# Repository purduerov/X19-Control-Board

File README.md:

# X19 Control Board

Primary microcontroller board managing actuator actuation, telemetry collection, and vehicle subsystem communication for the Purdue ROV X19 vehicle.

---

## 🚀 Quickstart: Opening the Project (Recommended)

**Always open the project using the 1-click launcher:**

* **Windows:** Double-click `LAUNCH_KICAD.bat`
* **macOS / Linux:** Run `./LAUNCH_KICAD.sh`

### What the Launcher Does Automatically:
1. ⚙️ **Configures Git Hooks & Clean Filters:** Sets up Git to strip volatile viewport/zoom coordinates on every commit, preventing merge conflicts.
2. 🔄 **Auto-Updates Component Library:** Pulls the freshest symbols, footprints, and 3D models from `purdue-rov-kicad-lib` before opening.
3. 📐 **Opens KiCad:** Launches `X19-Control-Board.kicad_pro` with all 6 central library categories pre-linked.

---

## Cloning the Repository
Clone recursively to ensure the central component library is initialized:
```bash
git clone --recursive https://github.com/purduerov/X19-Control-Board.git
cd X19-Control-Board
```

## Central Component Library & Manager GUI

The project links to the central `purdue-rov-kicad-lib` submodule mapped across 6 categories in `sym-lib-table` and `fp-lib-table`:
- `rov_passives`: Resistors, capacitors, inductors, crystals
- `rov_power`: Voltage regulators, buck/boost converters, MOSFETs, diodes
- `rov_logic`: MCUs, logic ICs, op-amps, drivers, level shifters
- `rov_connectors`: Power terminals, XT60, headers, USB, JST connectors
- `rov_sensors`: IMUs, temperature, pressure sensors
- `rov_mech`: Mounting holes, standoffs, test points

### Launching the Library Manager GUI
To browse parts, inspect footprints, edit properties, or add/delete components in the shared library:
- **Windows:** Double-click `libs\purdue-rov-kicad-lib\LIBRARY_MANAGER.bat`
- **macOS / Linux:** Run `./libs/purdue-rov-kicad-lib/LIBRARY_MANAGER.sh`

## Design Rules & Clearances

- Clearance and isolation constraints are configured in `custom_rules.kicad_dru`.
- All symbols and footprints must comply with central library guidelines.

## Automated CI/CD & DevOps Preflight Checks

All CI/CD automation and tooling are centralized in [`purduerov/pcb-devops`](https://github.com/purduerov/pcb-devops):
1. **Automated Git Clean Filters:** Configured automatically by `.githooks/pre-commit` to prevent viewport/zoom merge noise.
2. **KiCad Symbol Linting:** Validates mandatory fields (`MPN`, `Manufacturer`, `Category`, `DigiKey`, `Datasheet`, `Temp_Range`) on all library components.
3. **ERC & DRC Validation:** Executes Electrical and Design Rules Checks via KiBot in GitHub Actions.
4. **Artifact Generation:** Automatically exports Schematic PDFs, Board Layout PDFs, and Interactive HTML BOMs on every pull request.

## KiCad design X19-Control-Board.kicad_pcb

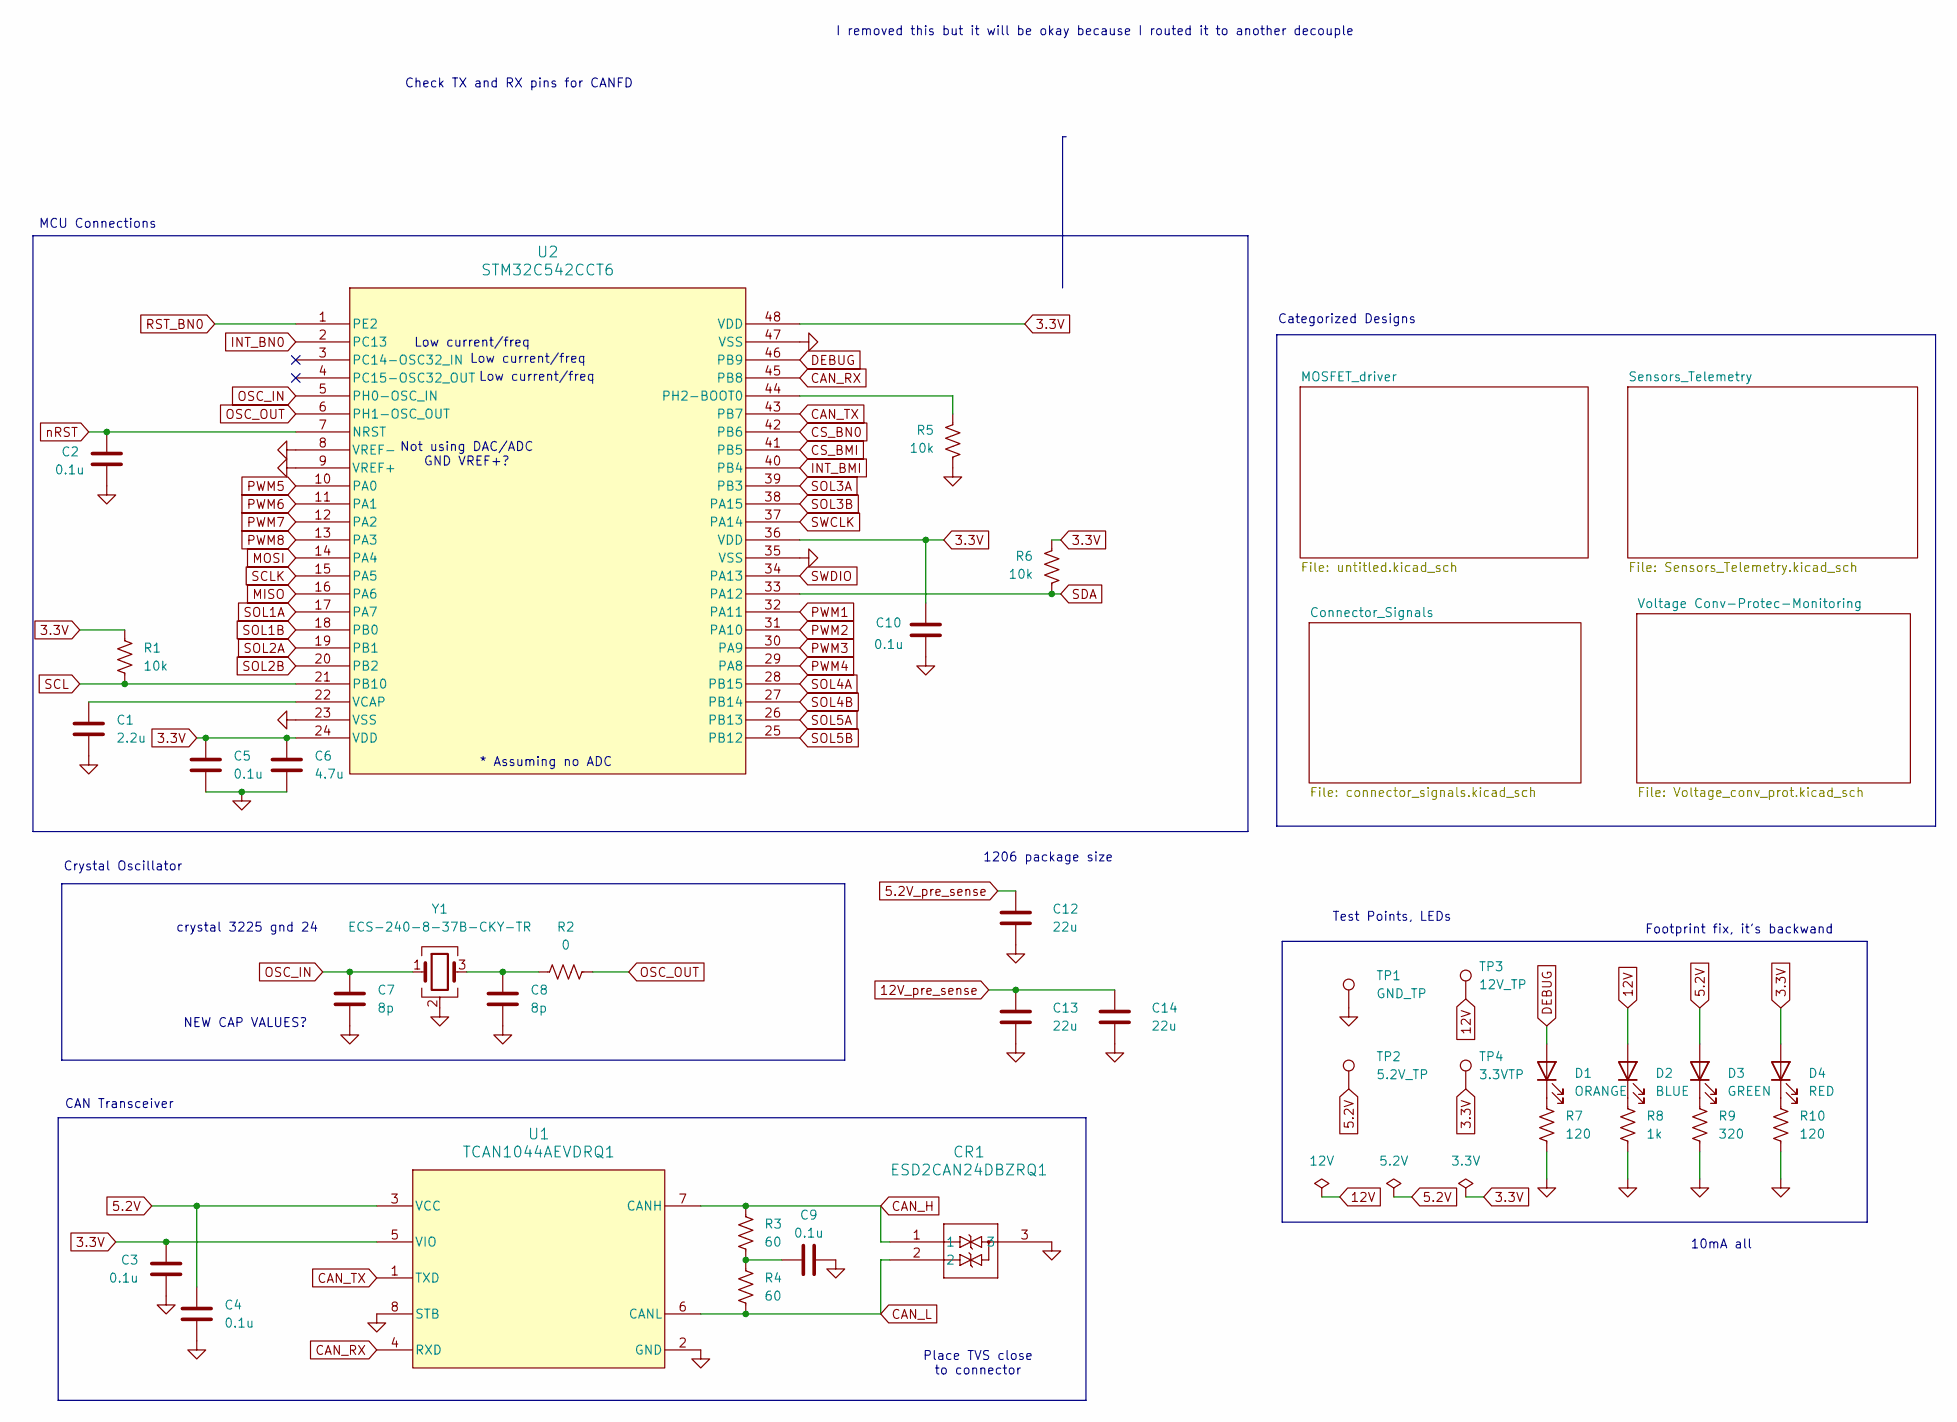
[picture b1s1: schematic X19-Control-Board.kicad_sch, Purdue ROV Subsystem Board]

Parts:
C1: 2.2u; C_0603_1608Metric_Pad1.08x0.95mm_HandSolder
C2, C3, C4, C5, C9, C10: 0.1u; C_0603_1608Metric_Pad1.08x0.95mm_HandSolder
C6: 4.7u; C_0603_1608Metric_Pad1.08x0.95mm_HandSolder
C7, C8: 8p; C_0603_1608Metric_Pad1.08x0.95mm_HandSolder
C12, C13, C14: 22u; C_1206_3216Metric_Pad1.33x1.80mm_HandSolder
CR1: ESD2CAN24DBZRQ1
D1: ORANGE; LTST-C191KFKT_1_anode_2_cathode
D2: BLUE; LTST-C191KFKT_1_anode_2_cathode
D3: GREEN; LTST-C191KFKT_1_anode_2_cathode
D4: RED; LTST-C191KFKT_1_anode_2_cathode
R1, R5, R6: 10k; R_0603_1608Metric_Pad0.98x0.95mm_HandSolder
R2: 0; R_0603_1608Metric_Pad0.98x0.95mm_HandSolder
R3, R4: 60; R_0603_1608Metric_Pad0.98x0.95mm_HandSolder
R7, R10: 120; R_0603_1608Metric_Pad0.98x0.95mm_HandSolder
R8: 1k; R_0603_1608Metric_Pad0.98x0.95mm_HandSolder
R9: 320; R_0603_1608Metric_Pad0.98x0.95mm_HandSolder
TP1: GND_TP; TestPoint_Pad_D3.0mm
TP2: 5.2V_TP; TestPoint_Pad_D3.0mm
TP3: 12V_TP; TestPoint_Pad_D3.0mm
TP4: 3.3VTP; TestPoint_Pad_D3.0mm
U1: TCAN1044AEVDRQ1
U2: STM32C542CCT6
Y1: ECS-240-8-37B-CKY-TR; ECS-240-8-37CKM_ECS

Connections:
3.3V: C3.1, C5.1, C6.1, C10.2, D4.2 (A), R1.1, R6.1, TP4.1 (1_1), U1.5 (VIO), U2.24 (VDD), U2.36 (VDD), U2.48 (VDD); also elsewhere on the board
5.2V: C4.1, D3.2 (A), TP2.1 (1_1), U1.3 (VCC); also elsewhere on the board
5.2V_pre_sense: C12.1; also elsewhere on the board
12V: D2.2 (A), TP3.1 (1_1); also elsewhere on the board
12V_pre_sense: C13.1, C14.1; also elsewhere on the board
CAN_H: CR1.1, R3.1, U1.7 (CANH); also elsewhere on the board
CAN_L: CR1.2, R4.2, U1.6 (CANL); also elsewhere on the board
CAN_RX: U1.4 (RXD), U2.45 (PB8)
CAN_TX: U1.1 (TXD), U2.43 (PB7)
CS_BMI: U2.41 (PB5); also elsewhere on the board
CS_BN0: U2.42 (PB6); also elsewhere on the board
DEBUG: D1.2 (A), U2.46 (PB9)
GND: C1.2, C2.1, C3.2, C4.2, C5.2, C6.2, C7.2, C8.2, C9.2, C10.1, C12.2, C13.2, C14.2, CR1.3, R5.2, R7.2, R8.2, R9.2, R10.2, TP1.1 (1_1), U1.2 (GND), U1.8 (STB), U2.8 (VREF-), U2.9 (VREF+), U2.23 (VSS), U2.35 (VSS), U2.47 (VSS), Y1.2 (G), Y1.4 (G); also elsewhere on the board
INT_BMI: U2.40 (PB4); also elsewhere on the board
INT_BN0: U2.2 (PC13); also elsewhere on the board
MISO: U2.16 (PA6); also elsewhere on the board
MOSI: U2.14 (PA4); also elsewhere on the board
unnamed: C8.1, R2.1, Y1.3
unnamed: C9.1, R3.2, R4.1
unnamed: D1.1 (K), R7.1
unnamed: D2.1 (K), R8.1
unnamed: D3.1 (K), R9.1
unnamed: D4.1 (K), R10.1
unnamed: R5.1, U2.44 (PH2-BOOT0)
unnamed: C1.1, U2.22 (VCAP)
OSC_IN: C7.1, U2.5 (PH0-OSC_IN), Y1.1
OSC_OUT: R2.2, U2.6 (PH1-OSC_OUT)
PWM1: U2.32 (PA11); also elsewhere on the board
PWM2: U2.31 (PA10); also elsewhere on the board
PWM3: U2.30 (PA9); also elsewhere on the board
PWM4: U2.29 (PA8); also elsewhere on the board
PWM5: U2.10 (PA0); also elsewhere on the board
PWM6: U2.11 (PA1); also elsewhere on the board
PWM7: U2.12 (PA2); also elsewhere on the board
PWM8: U2.13 (PA3); also elsewhere on the board
RST_BN0: U2.1 (PE2); also elsewhere on the board
SCL: R1.2, U2.21 (PB10); also elsewhere on the board
SCLK: U2.15 (PA5); also elsewhere on the board
SDA: R6.2, U2.33 (PA12); also elsewhere on the board
SOL1A: U2.17 (PA7); also elsewhere on the board
SOL1B: U2.18 (PB0); also elsewhere on the board
SOL2A: U2.19 (PB1); also elsewhere on the board
SOL2B: U2.20 (PB2); also elsewhere on the board
SOL3A: U2.39 (PB3); also elsewhere on the board
SOL3B: U2.38 (PA15); also elsewhere on the board
SOL4A: U2.28 (PB15); also elsewhere on the board
SOL4B: U2.27 (PB14); also elsewhere on the board
SOL5A: U2.26 (PB13); also elsewhere on the board
SOL5B: U2.25 (PB12); also elsewhere on the board
SWCLK: U2.37 (PA14); also elsewhere on the board
SWDIO: U2.34 (PA13); also elsewhere on the board
nRST: C2.2, U2.7 (NRST); also elsewhere on the board

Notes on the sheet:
Test Points, LEDs
Low current/freq
I removed this but it will be okay because I routed it to another decouple
CAN Transceiver
* Assuming no ADC
1206 package size
Crystal Oscillator
Not using DAC/ADC GND VREF+?
NEW CAP VALUES?
Check TX and RX pins for CANFD
MCU Connections
10mA all
crystal 3225 gnd 24
Footprint fix, it's backwand
Place TVS close to connector
Categorized Designs

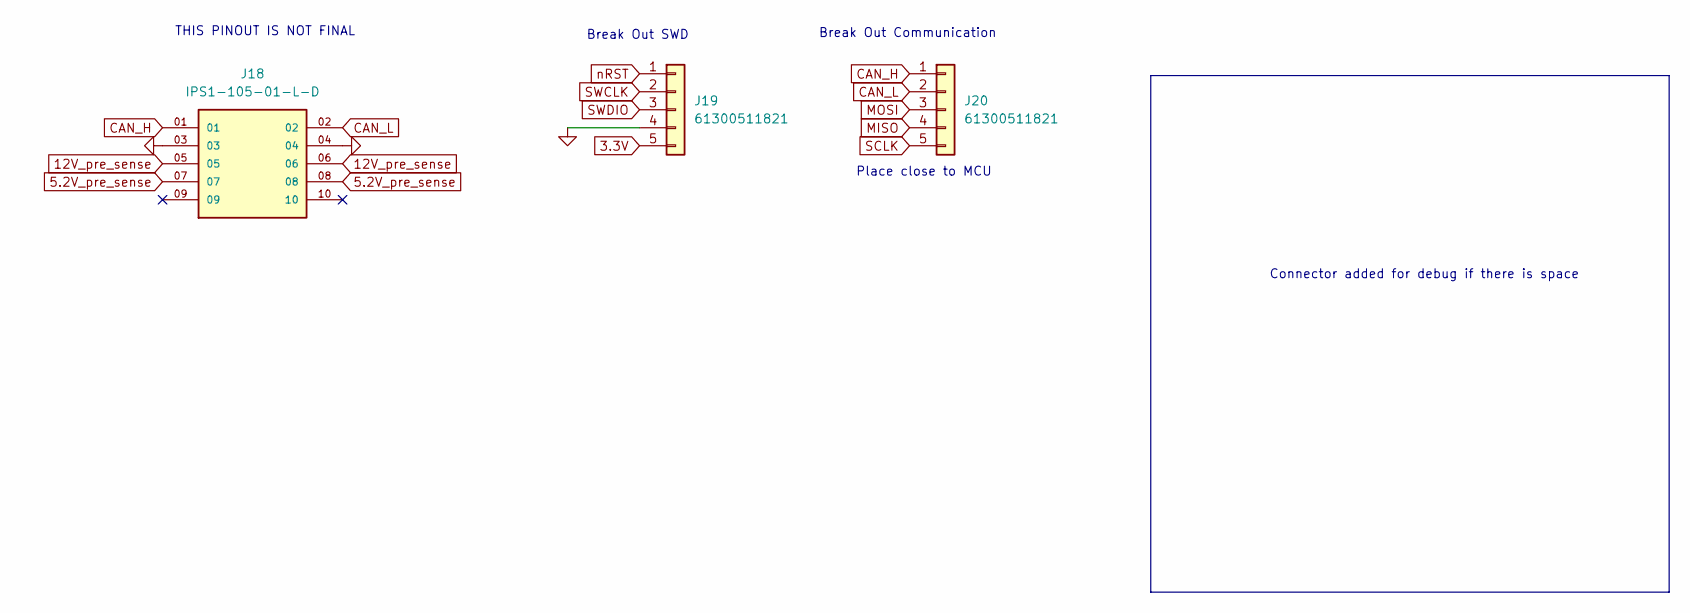
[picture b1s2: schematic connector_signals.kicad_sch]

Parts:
J18: IPS1-105-01-L-D; SAMTEC_IPS1-105-01-S-D; PARTREV R
J19, J20: 61300511821

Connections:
3.3V: J19.5; also elsewhere on the board
5.2V_pre_sense: J18.07, J18.08; also elsewhere on the board
12V_pre_sense: J18.05, J18.06; also elsewhere on the board
CAN_H: J18.01, J20.1; also elsewhere on the board
CAN_L: J18.02, J20.2; also elsewhere on the board
GND: J18.03, J18.04, J19.4; also elsewhere on the board
MISO: J20.4; also elsewhere on the board
MOSI: J20.3; also elsewhere on the board
SCLK: J20.5; also elsewhere on the board
SWCLK: J19.2; also elsewhere on the board
SWDIO: J19.3; also elsewhere on the board
nRST: J19.1; also elsewhere on the board

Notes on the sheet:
Break Out Communication
Place close to MCU
Connector added for debug if there is space
THIS PINOUT IS NOT FINAL
Break Out SWD

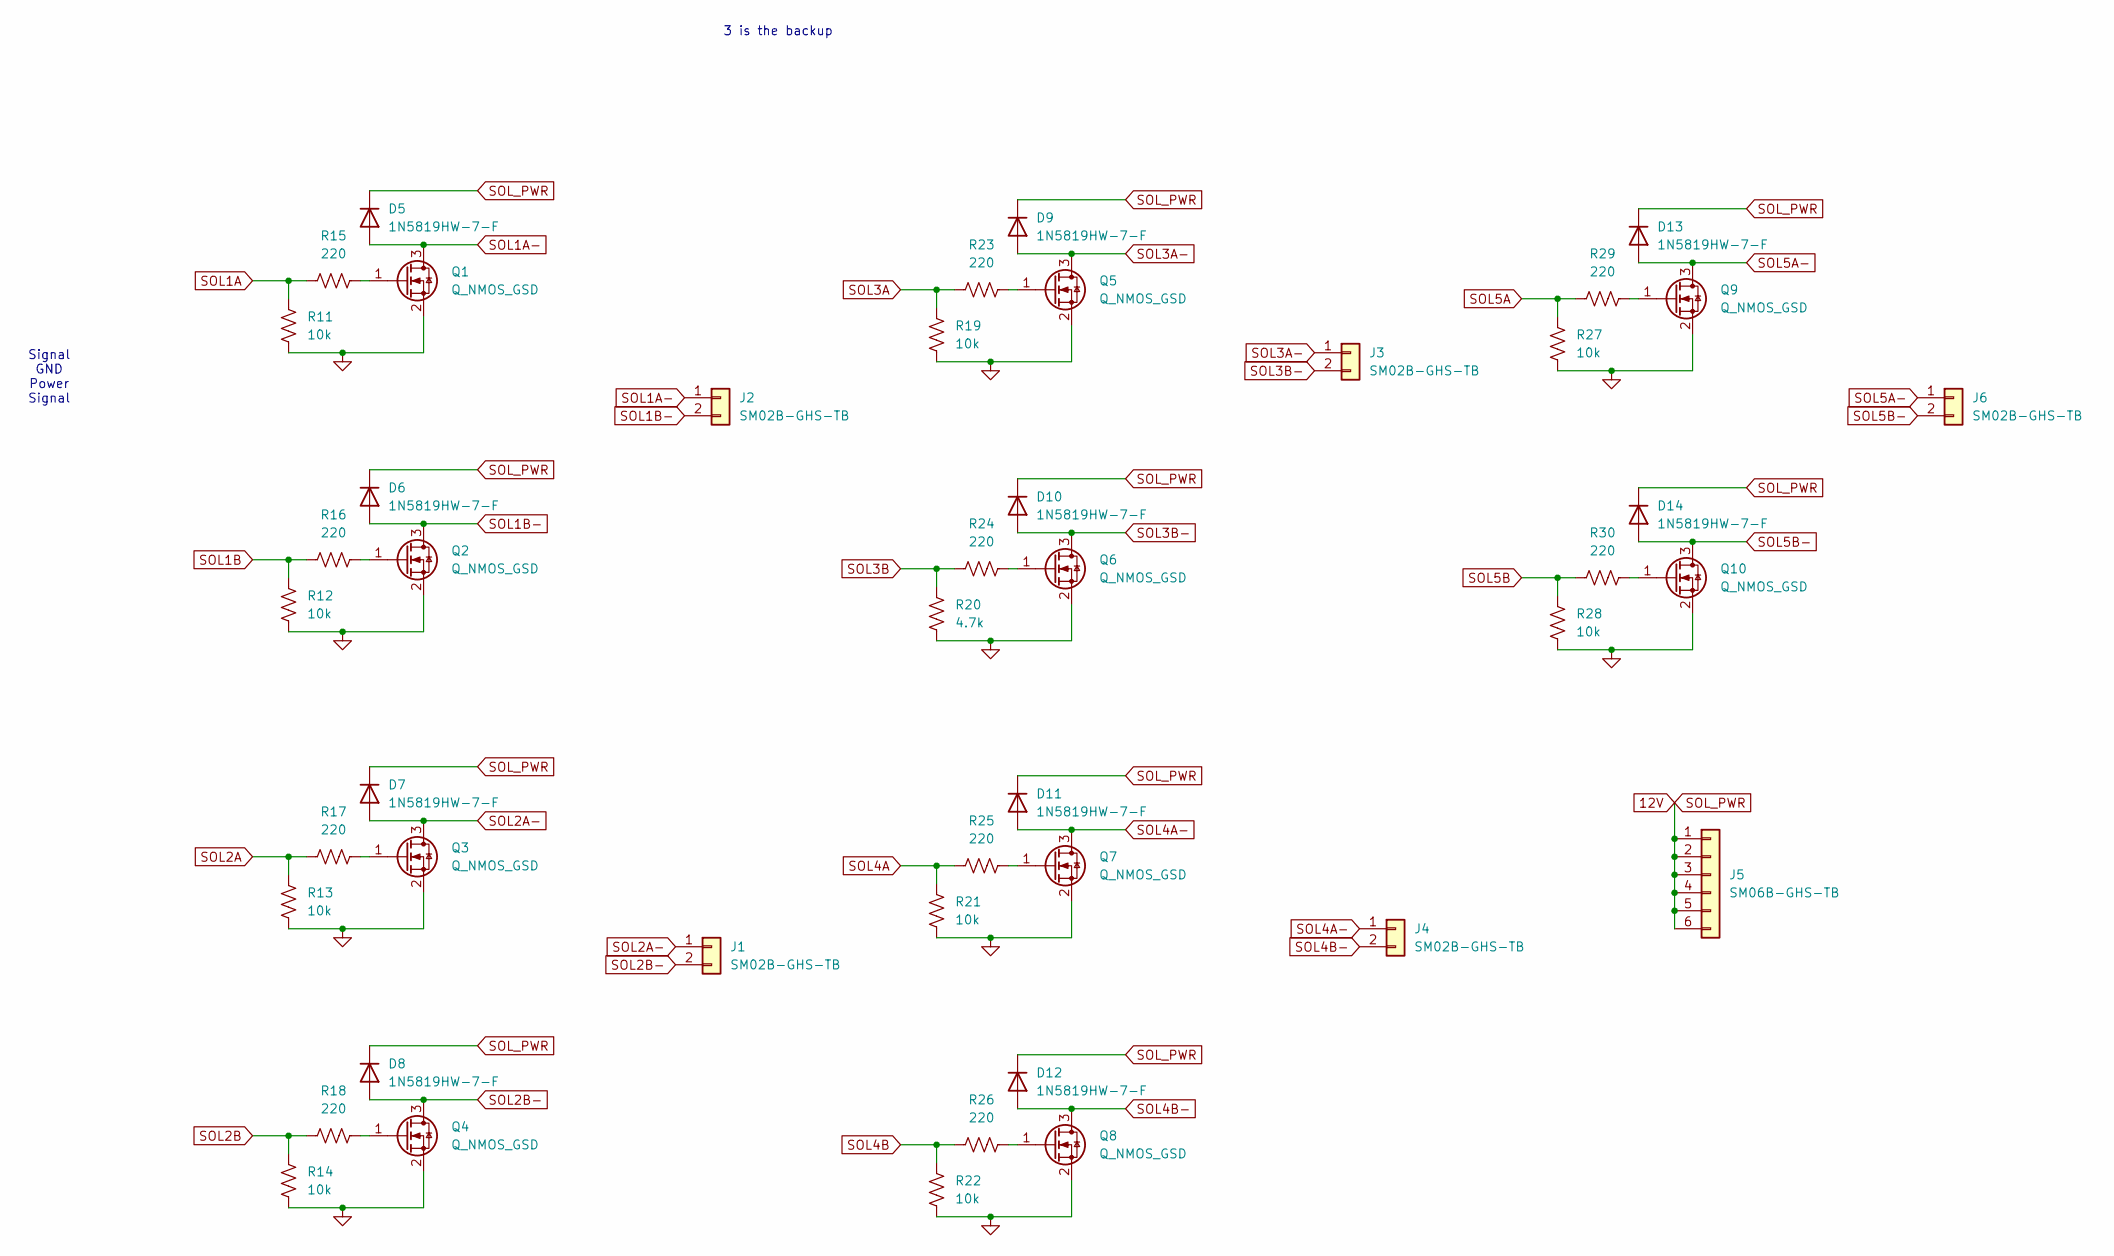
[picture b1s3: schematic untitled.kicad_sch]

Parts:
D5, D6, D7, D8, D9, D10, D11, D12, D13, D14: 1N5819HW-7-F; 1N5819HW-7-F_DIO
J1, J2, J3, J4, J6: SM02B-GHS-TB; Vertical_CONN_BM02B-GHS-TBT_JST
J5: SM06B-GHS-TB; vertical_CONN_BM06B-GHS-TBT_JST
Q1, Q2, Q3, Q4, Q5, Q6, Q7, Q8, Q9, Q10: Q_NMOS_GSD; SOT-23-3L_AOS
R11, R12, R13, R14, R19, R21, R22, R27, R28: 10k; R_0603_1608Metric_Pad0.98x0.95mm_HandSolder
R15, R16, R17, R18, R23, R24, R25, R26, R29, R30: 220; R_0603_1608Metric_Pad0.98x0.95mm_HandSolder
R20: 4.7k; R_0603_1608Metric_Pad0.98x0.95mm_HandSolder

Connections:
12V: D5.1 (K), D6.1 (K), D7.1 (K), D8.1 (K), D9.1 (K), D10.1 (K), D11.1 (K), D12.1 (K), D13.1 (K), D14.1 (K), J5.1, J5.2, J5.3, J5.4, J5.5, J5.6; also elsewhere on the board
GND: Q1.2 (S), Q2.2 (S), Q3.2 (S), Q4.2 (S), Q5.2 (S), Q6.2 (S), Q7.2 (S), Q8.2 (S), Q9.2 (S), Q10.2 (S), R11.2, R12.2, R13.2, R14.2, R19.2, R20.2, R21.2, R22.2, R27.2, R28.2; also elsewhere on the board
unnamed: Q1.1 (G), R15.2
unnamed: Q2.1 (G), R16.2
unnamed: Q3.1 (G), R17.2
unnamed: Q4.1 (G), R18.2
unnamed: Q5.1 (G), R23.2
unnamed: Q6.1 (G), R24.2
unnamed: Q7.1 (G), R25.2
unnamed: Q8.1 (G), R26.2
unnamed: Q9.1 (G), R29.2
unnamed: Q10.1 (G), R30.2
SOL1A: R11.1, R15.1; also elsewhere on the board
SOL1A-: D5.2 (A), J2.1, Q1.3 (D)
SOL1B: R12.1, R16.1; also elsewhere on the board
SOL1B-: D6.2 (A), J2.2, Q2.3 (D)
SOL2A: R13.1, R17.1; also elsewhere on the board
SOL2A-: D7.2 (A), J1.1, Q3.3 (D)
SOL2B: R14.1, R18.1; also elsewhere on the board
SOL2B-: D8.2 (A), J1.2, Q4.3 (D)
SOL3A: R19.1, R23.1; also elsewhere on the board
SOL3A-: D9.2 (A), J3.1, Q5.3 (D)
SOL3B: R20.1, R24.1; also elsewhere on the board
SOL3B-: D10.2 (A), J3.2, Q6.3 (D)
SOL4A: R21.1, R25.1; also elsewhere on the board
SOL4A-: D11.2 (A), J4.1, Q7.3 (D)
SOL4B: R22.1, R26.1; also elsewhere on the board
SOL4B-: D12.2 (A), J4.2, Q8.3 (D)
SOL5A: R27.1, R29.1; also elsewhere on the board
SOL5A-: D13.2 (A), J6.1, Q9.3 (D)
SOL5B: R28.1, R30.1; also elsewhere on the board
SOL5B-: D14.2 (A), J6.2, Q10.3 (D)

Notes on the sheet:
3 is the backup
Signal GND Power Signal

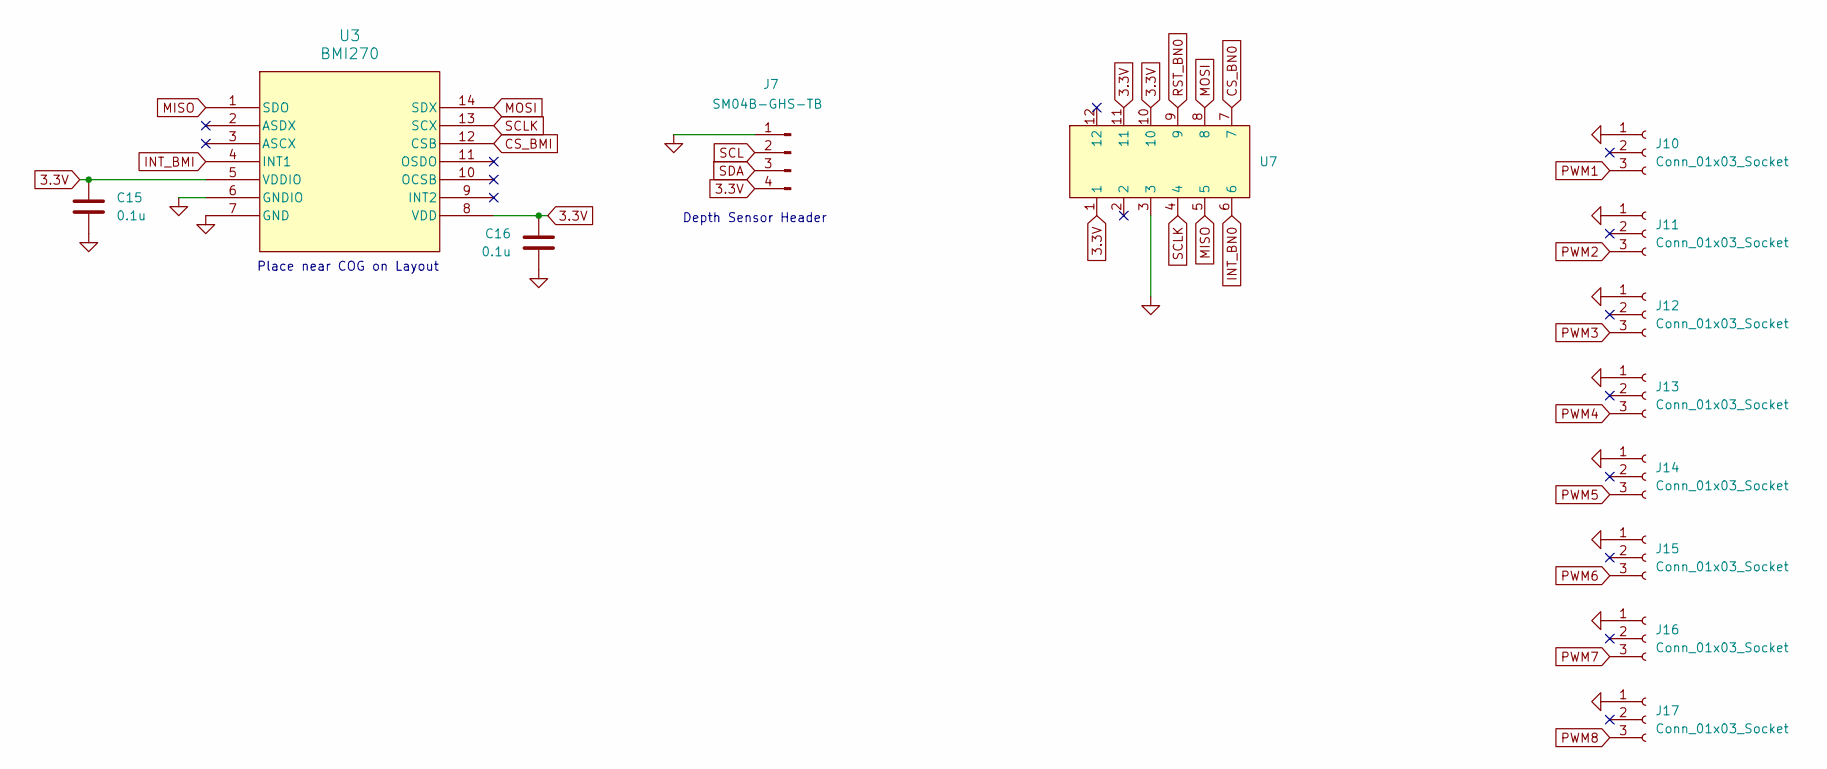
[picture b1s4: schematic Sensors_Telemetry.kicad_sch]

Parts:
C15, C16: 0.1u; C_0603_1608Metric_Pad1.08x0.95mm_HandSolder
J7: SM04B-GHS-TB; vertical_CONN_BM04B-GHS-TBT_JST
J10, J11, J12, J13, J14, J15, J16, J17: Conn_01x03_Socket; PinHeader_1x03_P2.54mm_Vertical
U3: BMI270; BMI270_BOS
U7: MODULE_4754

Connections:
3.3V: C15.1, C16.1, J7.4, U3.5 (VDDIO), U3.8 (VDD), U7.1, U7.10, U7.11; also elsewhere on the board
CS_BMI: U3.12 (CSB); also elsewhere on the board
CS_BN0: U7.7; also elsewhere on the board
GND: C15.2, C16.2, J7.1, J10.1, J11.1, J12.1, J13.1, J14.1, J15.1, J16.1, J17.1, U3.6 (GNDIO), U3.7 (GND), U7.3; also elsewhere on the board
INT_BMI: U3.4 (INT1); also elsewhere on the board
INT_BN0: U7.6; also elsewhere on the board
MISO: U3.1 (SDO), U7.5; also elsewhere on the board
MOSI: U3.14 (SDX), U7.8; also elsewhere on the board
PWM1: J10.3; also elsewhere on the board
PWM2: J11.3; also elsewhere on the board
PWM3: J12.3; also elsewhere on the board
PWM4: J13.3; also elsewhere on the board
PWM5: J14.3; also elsewhere on the board
PWM6: J15.3; also elsewhere on the board
PWM7: J16.3; also elsewhere on the board
PWM8: J17.3; also elsewhere on the board
RST_BN0: U7.9; also elsewhere on the board
SCL: J7.2; also elsewhere on the board
SCLK: U3.13 (SCX), U7.4; also elsewhere on the board
SDA: J7.3; also elsewhere on the board

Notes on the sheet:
Place near COG on Layout
Depth Sensor Header

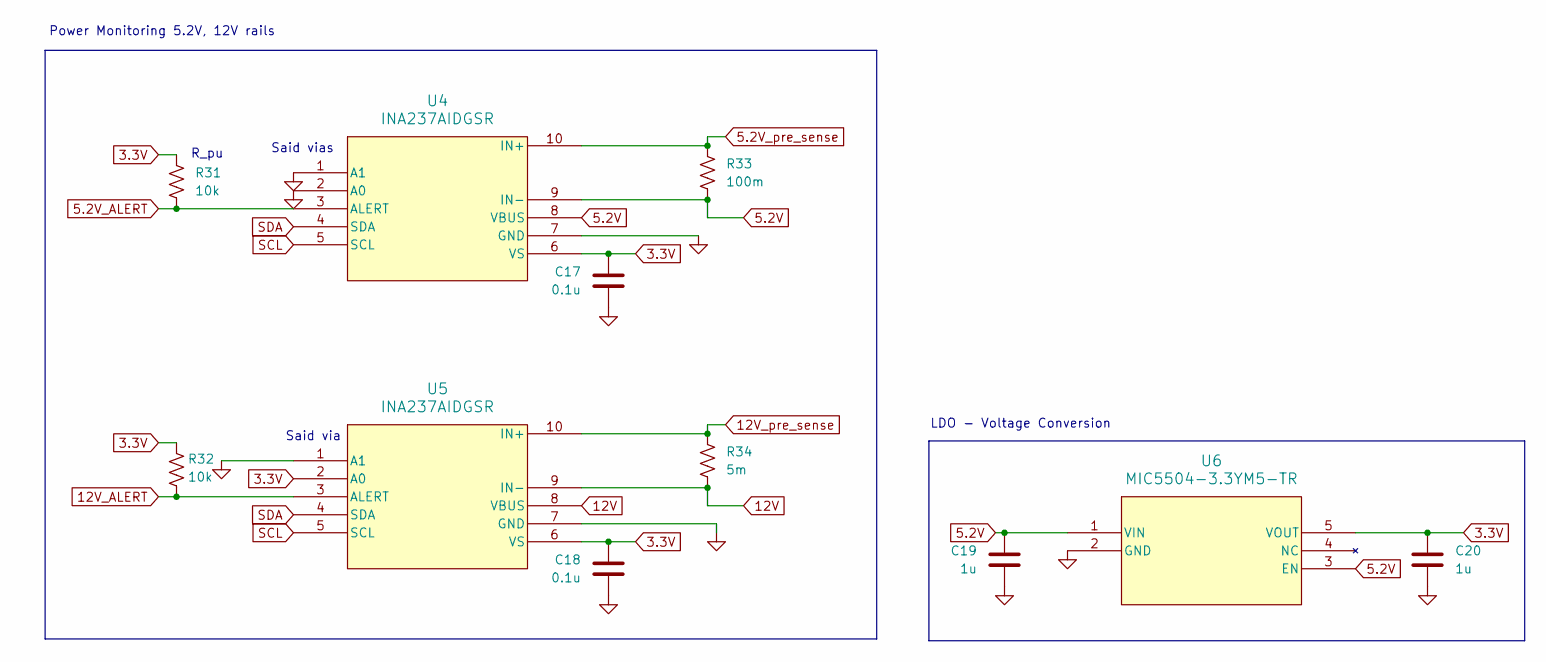
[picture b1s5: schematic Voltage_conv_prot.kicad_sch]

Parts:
C17, C18: 0.1u; C_0603_1608Metric_Pad1.08x0.95mm_HandSolder
C19, C20: 1u; C_0603_1608Metric_Pad1.08x0.95mm_HandSolder
R31, R32: 10k; R_0603_1608Metric_Pad0.98x0.95mm_HandSolder
R33: 100m; R_0603_1608Metric_Pad0.98x0.95mm_HandSolder
R34: 5m; R_0603_1608Metric_Pad0.98x0.95mm_HandSolder
U4, U5: INA237AIDGSR
U6: MIC5504-3.3YM5-TR; MIC5504_3_3YM5_TR

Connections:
3.3V: C17.1, C18.1, C20.1, R31.1, R32.1, U4.6 (VS), U5.2 (A0), U5.6 (VS), U6.5 (VOUT); also elsewhere on the board
5.2V: C19.1, R33.2, U4.8 (VBUS), U4.9 (IN-), U6.1 (VIN), U6.3 (EN); also elsewhere on the board
5.2V_ALERT: R31.2, U4.3 (ALERT)
5.2V_pre_sense: R33.1, U4.10 (IN+); also elsewhere on the board
12V: R34.2, U5.8 (VBUS), U5.9 (IN-); also elsewhere on the board
12V_ALERT: R32.2, U5.3 (ALERT)
12V_pre_sense: R34.1, U5.10 (IN+); also elsewhere on the board
GND: C17.2, C18.2, C19.2, C20.2, U4.1 (A1), U4.2 (A0), U4.7 (GND), U5.1 (A1), U5.7 (GND), U6.2 (GND); also elsewhere on the board
SCL: U4.5 (SCL), U5.5 (SCL); also elsewhere on the board
SDA: U4.4 (SDA), U5.4 (SDA); also elsewhere on the board

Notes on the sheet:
LDO - Voltage Conversion
Said via
R_pu
Said vias
Power Monitoring 5.2V, 12V rails

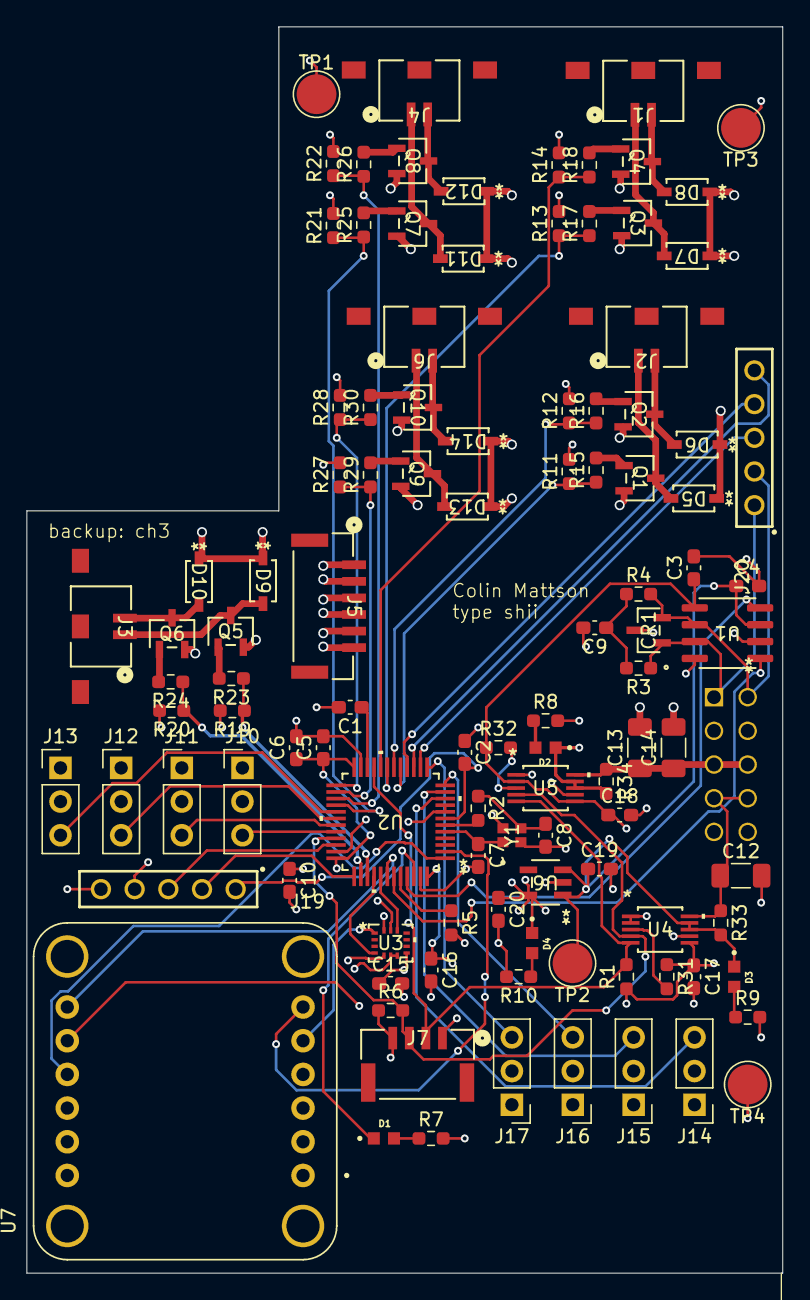
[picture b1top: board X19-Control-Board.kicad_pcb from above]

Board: 4 copper layers, 57.0 x 94.0 mm, 108 parts (1 on the bottom side), 74 nets.

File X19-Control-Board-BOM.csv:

Row,Description,Part,References,Value,Footprint,Quantity Per PCB,Status,Datasheet,KLC_S3.3,KLC_S4.1,Sim.Pins,PARTREV,STANDARD,MANUFACTURER,Sim.Device
1,Unpolarized capacitor,C,C7 C8,8p,C_0603_1608Metric_Pad1.08x0.95mm_HandSolder,2, ,,,,,,,,
2,Unpolarized capacitor,C,C2 C3 C4 C5 C9 C10 C11 C15 C16 C17 C18,0.1u,C_0603_1608Metric_Pad1.08x0.95mm_HandSolder,11, ,,,,,,,,
3,Unpolarized capacitor,C,C19 C20,1u,C_0603_1608Metric_Pad1.08x0.95mm_HandSolder,2, ,,,,,,,,
4,Unpolarized capacitor,C,C1,2.2u,C_0603_1608Metric_Pad1.08x0.95mm_HandSolder,1, ,,,,,,,,
5,Unpolarized capacitor,C,C6,4.7u,C_0603_1608Metric_Pad1.08x0.95mm_HandSolder,1, ,,,,,,,,
6,Unpolarized capacitor,C,C12 C13 C14,22u,C_1206_3216Metric_Pad1.33x1.80mm_HandSolder,3, ,,,,,,,,
7,,ESD2CAN24DBZRQ1,CR1,SOT-23_DBZ_TEX,ESD2CAN24DBZRQ1,1, ,ESD2CAN24DBZRQ1,,,,,,,
8,Diode,D,D5 D6 D7 D8 D9 D10 D11 D12 D13 D14,1N5819HW-7-F,1N5819HW-7-F_DIO,10, ,,,,1=K 2=A,,,,D
9,Light emitting diode,LED,D2,BLUE,LTST-C191KFKT_1_anode_2_cathode,1, ,,,,1=K 2=A,,,,
10,Light emitting diode,LED,D3,GREEN,LTST-C191KFKT_1_anode_2_cathode,1, ,,,,1=K 2=A,,,,
11,Light emitting diode,LED,D1,ORANGE,LTST-C191KFKT_1_anode_2_cathode,1, ,,,,1=K 2=A,,,,
12,Light emitting diode,LED,D4,RED,LTST-C191KFKT_1_anode_2_cathode,1, ,,,,1=K 2=A,,,,
13,"Generic connector, single row, 01x05, script generated (kicad-library-utils/schlib/autogen/connector/)",Conn_01x05,J19 J20,61300511821,61300511821,2, ,,,,,,,,
14,"Generic connector, single row, 01x03, script generated",Conn_01x03_Socket,J10 J11 J12 J13 J14 J15 J16 J17,Conn_01x03_Socket,PinHeader_1x03_P2.54mm_Vertical,8, ,,,,,,,,
15,,IPS1-105-01-L-D,J18,IPS1-105-01-L-D,SAMTEC_IPS1-105-01-S-D,1, ,,,,,R,Manufacturer Recommendations,Samtec,
16,"Generic connector, single row, 01x02, script generated (kicad-library-utils/schlib/autogen/connector/)",Conn_01x02,J1 J2 J3 J4 J6,SM02B-GHS-TB,Vertical_CONN_BM02B-GHS-TBT_JST,5, ,,,,,,,,
17,"Generic connector, single row, 01x04, script generated",Conn_01x04_Pin,J7,SM04B-GHS-TB,vertical_CONN_BM04B-GHS-TBT_JST,1, ,,,,,,,,
18,"Generic connector, single row, 01x06, script generated (kicad-library-utils/schlib/autogen/connector/)",Conn_01x06,J5,SM06B-GHS-TB,vertical_CONN_BM06B-GHS-TBT_JST,1, ,,,,,,,,
19,"N-MOSFET transistor, gate/source/drain",Q_NMOS_GSD,Q1 Q2 Q3 Q4 Q5 Q6 Q7 Q8 Q9 Q10,Q_NMOS_GSD,SOT-23-3L_AOS,10, ,,,,,,,,
20,"Resistor, US symbol",R_US,R2,0,R_0603_1608Metric_Pad0.98x0.95mm_HandSolder,1, ,,,,,,,,
21,"Resistor, US symbol",R_US,R34,5m,R_0603_1608Metric_Pad0.98x0.95mm_HandSolder,1, ,,,,,,,,
22,"Resistor, US symbol",R_US,R33,100m,R_0603_1608Metric_Pad0.98x0.95mm_HandSolder,1, ,,,,,,,,
23,"Resistor, US symbol",R_US,R3 R4,60,R_0603_1608Metric_Pad0.98x0.95mm_HandSolder,2, ,,,,,,,,
24,"Resistor, US symbol",R_US,R7 R10,120,R_0603_1608Metric_Pad0.98x0.95mm_HandSolder,2, ,,,,,,,,
25,"Resistor, US symbol",R_US,R15 R16 R17 R18 R23 R24 R25 R26 R29 R30,220,R_0603_1608Metric_Pad0.98x0.95mm_HandSolder,10, ,,,,,,,,
26,"Resistor, US symbol",R_US,R9,320,R_0603_1608Metric_Pad0.98x0.95mm_HandSolder,1, ,,,,,,,,
27,"Resistor, US symbol",R_US,R8,1k,R_0603_1608Metric_Pad0.98x0.95mm_HandSolder,1, ,,,,,,,,
28,"Resistor, US symbol",R_US,R20,4.7k,R_0603_1608Metric_Pad0.98x0.95mm_HandSolder,1, ,,,,,,,,
29,"Resistor, US symbol",R_US,R1 R5 R6 R11 R12 R13 R14 R19 R21 R22 R27 R28 R31 R32,10k,R_0603_1608Metric_Pad0.98x0.95mm_HandSolder,14, ,,,,,,,,
30,,BMI270,U3,BMI270,BMI270_BOS,1, ,BMI270,,,,,,,
31,,STM32C542CCT6,U2,LQFP48-7X7,STM32C542CCT6,1, ,https://www.st.com/resource/en/datasheet/stm32c542cc.pdf,,,,,,,
32,,MIC5504-3.3YM5-TR,U6,MIC5504-3.3YM5-TR,MIC5504_3_3YM5_TR,1, ,MIC5504-3.3YM5-TR,,,,,,,
33,,TCAN1044VDRQ1,U1,TCAN1044A_TEX,TCAN1044AEVDRQ1,1, ,https://www.ti.com/lit/gpn/tcan1044-q1,,,,,,,
34,,INA237AIDGSR,U4 U5,VSSOP_IDGSR_TEX,INA237AIDGSR,2, ,https://www.ti.com/lit/gpn/ina237,,,,,,,
35,,BN0_Colin_made,U7,~,MODULE_4754,1, ,,,,,2021-03-16,Manufacturer Recommendations,Adafruit,
36,"Four pin crystal, GND on pins 2 and 4",Crystal_GND24,Y1,ECS-240-8-37B-CKY-TR,ECS-240-8-37CKM_ECS,1, ,,The rectangle is not a symbol body but a graphical element,Some pins are on 50mil grid to make the symbol small,,,,,





Project info:
Schematic:,X19-Control-Board
Variant:,default
Revision:,
Date:,2026-11-05_20-38-01
KiCad Version:,10.0.5-unknown-202607221313~667fa36054~ubuntu25.10.1
Statistics:
Component Groups:,36
Component Count:,105
Fitted Components:,105
Number of PCBs:,1
Total Components:,105
